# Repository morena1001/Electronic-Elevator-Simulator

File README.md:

# Electronic-Elevator-Simulator

This project simulates a single elevator that services a three floor building. A guest is able to request usage of the elevator in any floor, which will either be serviced immediately by the elevator, or be picked up while the elevator is on route to a destination in another floor. Inside the elevator, a guest is able to choose a not already chosen destination. This project was developed using an STM32F302R8 alongside a PCB housing the external buttons and LEDs.

In terms of inputs, there are a total of 7 input buttons. The first 4 correspond to the request buttons located outside of the elevator (one each for floors 1 and 3, which only go in one direction, and two for floor 2, which guests can choose to go upwards or downwards from). The other 3 inputs buttons  correspond to the destination buttons located inside of the elevator (one for each floor). 

In terms of outputs, there are a total of 12 LEDs. The first 3 display the current position of the elevator (one for each floor), the next 3 display the current destination of the elevator (one for each floor), the next 2 display the current direction of the elevator (one for each possible direction, up and down), the next 3 correspond to the request made to use the elevator (one for each floor), and the last LED blinks at regular intervals to show that a destination can be chosen.

## GPIO PERIPHERALS

**_PB0_** - CN7 pin 34, A3

Defined as II1 in the program, or _Inside Interface 1_, this pin connects to the external button in charge of setting floor 1 as a destination.

**_PB1_** - CN10 pin 24, D8

Defined as II2 in the program, this pin connects to the external button in charge of setting floor 2 as a destination.

**_PB2_** - CN10 pin 22, D7

Defined as II3 in the program, this pin connects to the external button in charge of setting floor 3 as a destination.

**_PB3_** - CN10 pin 31, D3

Defined as OI1U, or _Outside Interface 1 Up_, this pin connects to the external button in charge of requesting floor 1 with an upward direction.

**_PB4_** - CN10 pin 27, D5

Defined as OI2D, or _Outside Interface 2 Down_, this pin connects to the external button in charge of requesting floor 2 with a downward direction.

**_PB5** - CN10 pin 29, D4

Defined as OI2U, this pin connects to the external button in charge of requesting floor 2 with an upward direction.

**_PB6_** - CN10 pin 17, D10

Defined as OI3D, this pin connects to the external button in charge of requesting floor 3 with a downward direction.

**_PC0_** - CN7 pin 38, A5

Defined as PF1, or _Position Floor 1_, this pin connects to the external LED in charge of displaying floor 1 as the elevator's current position.

**_PC1_** - CN7 pin 36, A4

Defined as PF2, this pin connects to the external LED in charge of displaying floor 2 as the elevator's current position.

**_PC2_** - CN7 pin 35, A4

Defined as PF3, this pin connects to the external LED in charge of displaying floor 3 as the elevator's current position.

**_PC3_** - CN7 pin 37, A5

Defined as DF1, or _Destination Floor 1_, this pin connects to the external LED in charge of displaying floor 1 as a destination.

**_PC4_** - CN10 pin 34,D2

Defined as DF2, this pin connects to the external LED in charge of displaying floor 2 as a destination.

**_PC5_** - CN10 pin 6, D14

Defined as DF3, this pin connects to the external LED in charge of displaying floor 3 as a destination.

**_PC6_** - CN10 pin 4, D15

Defined as DU, or _Direction Up_, this pin connects to the external LED in charge of displaying the elevator's upward direction when moving.

**_PC7_** - CN10 pin 19, D9

Defined as DD, or _Direction Down_, this pin connects to the external LED in charge of displaying the elevator's downward direction when moving.

**_PC8_** - CN10 pin 2, above D15

Defined as FR1, or _Floor Request 1_, this pins connects to the external LED in charge of displaying floor 1's request to use the elevator.

**_PC9_** - CN10 pin 1, above D15

Defined as FR2, this pins connects to the external LED in charge of displaying floor 2's request to use the elevator.

**_PC10_** - CN7 pin 1

Defined as FR3, this pins connects to the external LED in charge of displaying floor 3's request to use the elevator.

**_PC11_** - CN7 pin 2

Defined as BCDI, or _Button Choose Destination Indicator_, this pin connects to the external LED in charge of blinking a certain pattern to show that a destination can be chosen.

## BUTTON AND LED GPIO CONFIGURATIONS

All of the external buttons are configured as follows. GPIO mode is set to "External Interrupt Mode with Rising edge trigger detection", and GPIO Pull-up/Pull-down is set to "Pull up". All of the external LEDs are configured as follows. GPIO output level is set to "Low", GPIO mode is set to "Output Push Pull", GPIO Pull-up/Pull-down is set to "No pull-up and no pull-down" and Maximum output speed is set to "Low".

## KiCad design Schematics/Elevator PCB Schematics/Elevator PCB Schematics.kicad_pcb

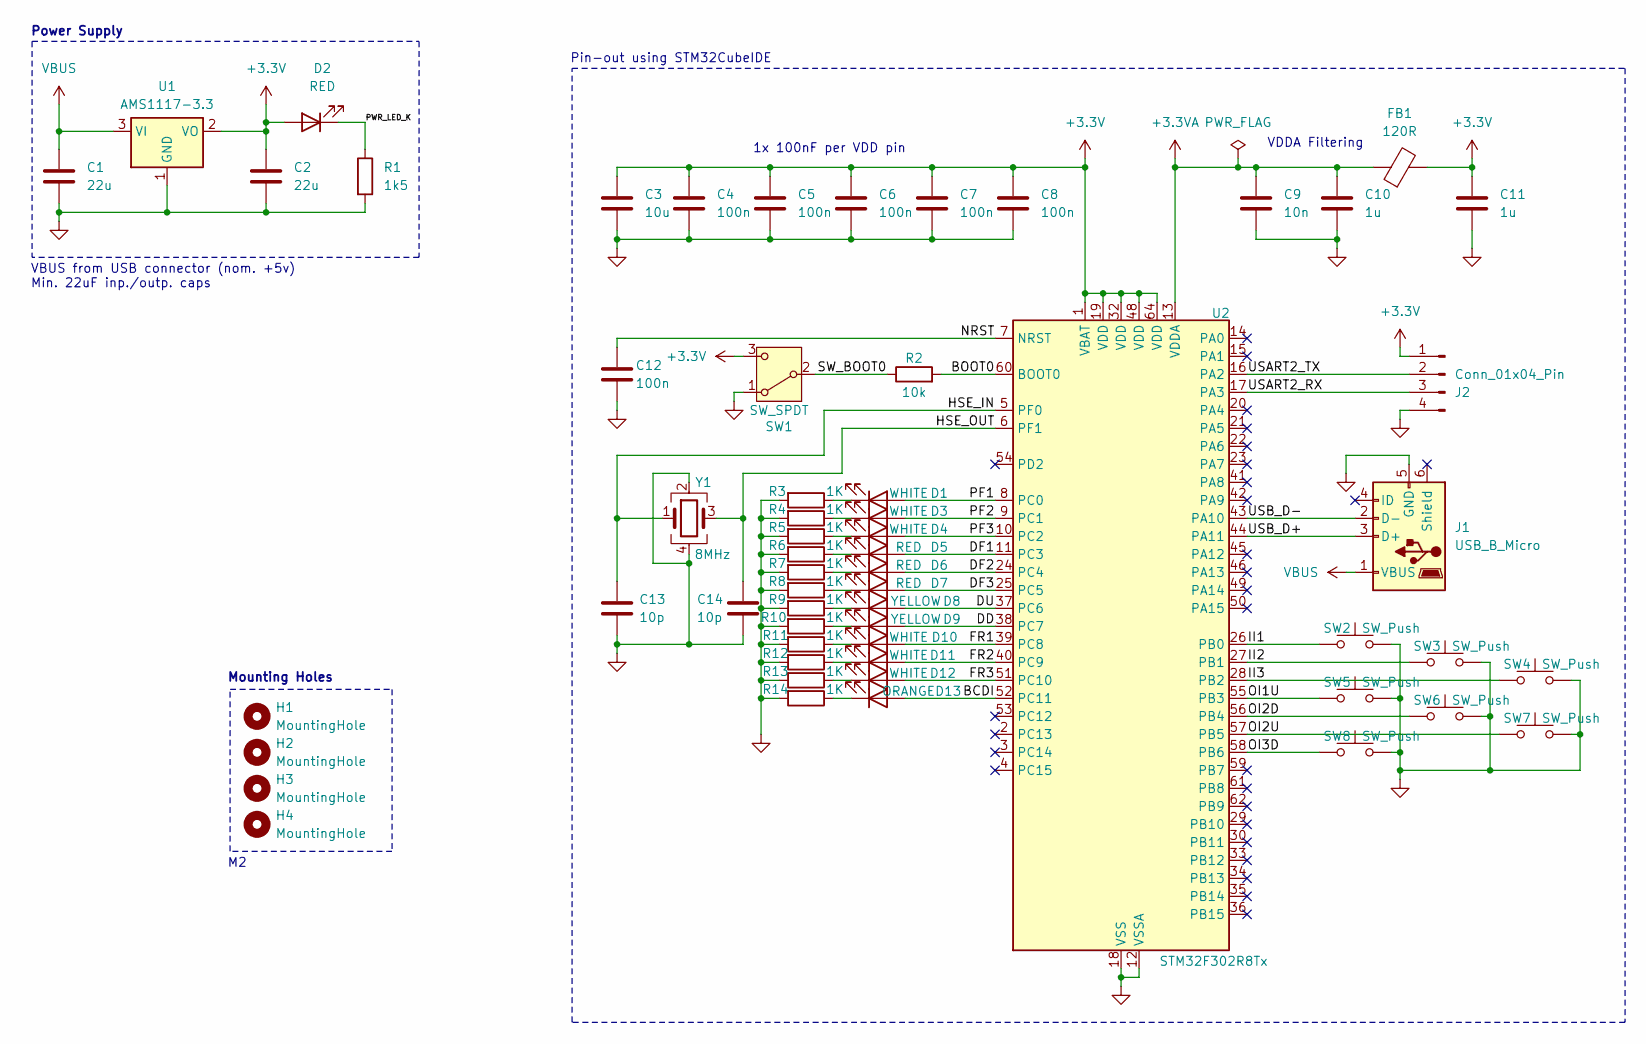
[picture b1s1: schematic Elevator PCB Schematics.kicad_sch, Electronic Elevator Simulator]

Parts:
C1, C2: 22u; C_0805_2012Metric
C3: 10u; C_0603_1608Metric
C4, C5, C6, C7, C8, C12: 100n; C_0402_1005Metric
C9: 10n; C_0402_1005Metric
C10, C11: 1u; C_0402_1005Metric
C13, C14: 10p; C_0402_1005Metric
D1, D3, D4, D10, D11, D12: WHITE; LED_0603_1608Metric
D2, D5, D6, D7: RED; LED_0603_1608Metric
D8, D9: YELLOW; LED_0603_1608Metric
D13: ORANGE; LED_0603_1608Metric
FB1: 120R; L_0603_1608Metric
H1, H2, H3, H4: MountingHole; MountingHole_2.2mm_M2
J1: USB_B_Micro; USB_Micro-B_Wuerth_629105150521
J2: Conn_01x04_Pin; PinHeader_1x04_P2.54mm_Vertical
R1: 1k5; R_0402_1005Metric
R2: 10k; R_0402_1005Metric
R3, R4, R5, R6, R7, R8, R9, R10, R11, R12, R13, R14: 1K; R_0402_1005Metric
SW1: SW_SPDT; SW_SPDT_PCM12
SW2, SW3, SW4, SW5, SW6, SW7, SW8: SW_Push; SW_PUSH_6mm_H5mm
U1: AMS1117-3.3; SOT-223-3_TabPin2
U2: STM32F302R8Tx; LQFP-64_10x10mm_P0.5mm
Y1: 8MHz; Crystal_SMD_0603-4Pin_6.0x3.5mm

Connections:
+3.3V: C2.1, C3.1, C4.1, C5.1, C6.1, C7.1, C8.1, C11.1, D2.2 (A), FB1.2, J2.1, SW1.3 (C), U1.2 (VO), U2.1 (VBAT), U2.19 (VDD), U2.32 (VDD), U2.48 (VDD), U2.64 (VDD)
+3.3VA: C9.1, C10.1, FB1.1, U2.13 (VDDA)
/BCDI: D13.2 (A), U2.52 (PC11)
/BOOT0: R2.2, U2.60 (BOOT0)
/DD: D9.2 (A), U2.38 (PC7)
/DF1: D5.2 (A), U2.11 (PC3)
/DF2: D6.2 (A), U2.24 (PC4)
/DF3: D7.2 (A), U2.25 (PC5)
/DU: D8.2 (A), U2.37 (PC6)
/FR1: D10.2 (A), U2.39 (PC8)
/FR2: D11.2 (A), U2.40 (PC9)
/FR3: D12.2 (A), U2.51 (PC10)
/HSE_IN: C13.1, U2.5 (PF0), Y1.1
/HSE_OUT: C14.1, U2.6 (PF1), Y1.3
/II1: SW2.1, U2.26 (PB0)
/II2: SW3.1, U2.27 (PB1)
/II3: SW4.1, U2.28 (PB2)
/NRST: C12.1, U2.7 (NRST)
/OI1U: SW5.1, U2.55 (PB3)
/OI2D: SW6.1, U2.56 (PB4)
/OI2U: SW7.1, U2.57 (PB5)
/OI3D: SW8.1, U2.58 (PB6)
/PF1: D1.2 (A), U2.8 (PC0)
/PF2: D3.2 (A), U2.9 (PC1)
/PF3: D4.2 (A), U2.10 (PC2)
/PWR_LED_K: D2.1 (K), R1.1
/SW_BOOT0: R2.1, SW1.2 (B)
/USART2_RX: J2.3, U2.17 (PA3)
/USART2_TX: J2.2, U2.16 (PA2)
/USB_D+: J1.3 (D+), U2.44 (PA11)
/USB_D-: J1.2 (D-), U2.43 (PA10)
GND: C1.2, C2.2, C3.2, C4.2, C5.2, C6.2, C7.2, C8.2, C9.2, C10.2, C11.2, C12.2, C13.2, C14.2, J1.5 (GND), J2.4, R1.2, R3.2, R4.2, R5.2, R6.2, R7.2, R8.2, R9.2, R10.2, R11.2, R12.2, R13.2, R14.2, SW1.1 (A), SW2.2, SW3.2, SW4.2, SW5.2, SW6.2, SW7.2, SW8.2, U1.1 (GND), U2.12 (VSSA), U2.18 (VSS), U2.31 (VSS), U2.47 (VSS), U2.63 (VSS), Y1.2, Y1.4
unnamed: D1.1 (K), R3.1
unnamed: D3.1 (K), R4.1
unnamed: D4.1 (K), R5.1
unnamed: D5.1 (K), R6.1
unnamed: D6.1 (K), R7.1
unnamed: D7.1 (K), R8.1
unnamed: D8.1 (K), R9.1
unnamed: D9.1 (K), R10.1
unnamed: D10.1 (K), R11.1
unnamed: D11.1 (K), R12.1
unnamed: D12.1 (K), R13.1
unnamed: D13.1 (K), R14.1
VBUS: C1.1, J1.1 (VBUS), U1.3 (VI)

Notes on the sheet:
Power Supply
Pin-out using STM32CubeIDE
VDDA Filtering
1x 100nF per VDD pin
Mounting Holes
VBUS from USB connector (nom. +5v) Min. 22uF inp./outp. caps

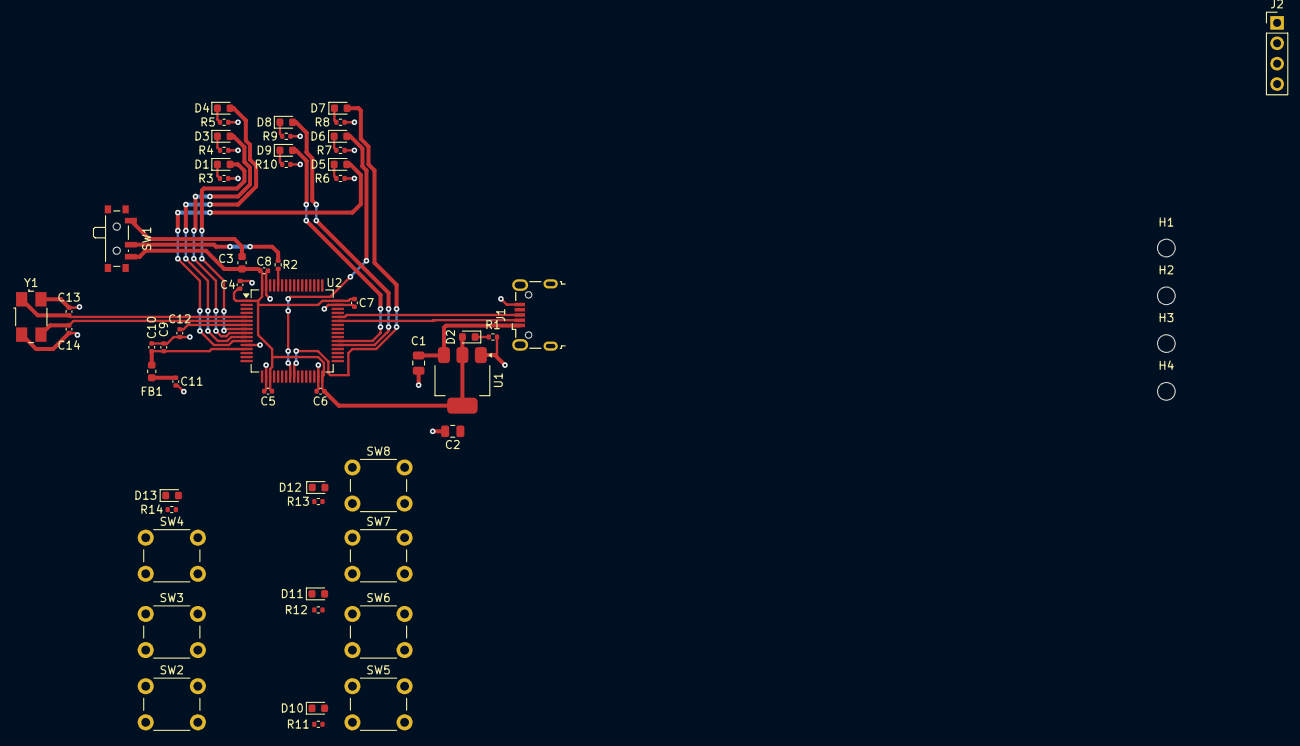
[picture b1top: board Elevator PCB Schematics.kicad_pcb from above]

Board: 2 copper layers, 59 parts (0 on the bottom side), 45 nets.

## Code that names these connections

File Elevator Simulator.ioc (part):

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Mcu.Name=STM32F302R(6-8)Tx
Mcu.Package=LQFP64
Mcu.UserName=STM32F302R8Tx
PA2.Mode=Asynchronous
PA2.Signal=USART2_TX
PA3.Mode=Asynchronous
PA3.Signal=USART2_RX
PB0.GPIOParameters=GPIO_PuPd,GPIO_Label,GPIO_ModeDefaultEXTI
PB0.GPIO_Label=II1 [Inside Interface 1]
PB0.GPIO_ModeDefaultEXTI=GPIO_MODE_IT_RISING
PB0.GPIO_PuPd=GPIO_PULLUP
PB0.Signal=GPXTI0
PB1.GPIOParameters=GPIO_PuPd,GPIO_Label,GPIO_ModeDefaultEXTI
PB1.GPIO_Label=II2 [Inside Interface 2]
PB1.GPIO_ModeDefaultEXTI=GPIO_MODE_IT_RISING
PB1.GPIO_PuPd=GPIO_PULLUP
PB1.Signal=GPXTI1
PB13.GPIOParameters=GPIO_Label
PB13.GPIO_Label=LD2 [Green Led]
PB13.Signal=GPIO_Output
PB2.GPIOParameters=GPIO_PuPd,GPIO_Label,GPIO_ModeDefaultEXTI
PB2.GPIO_Label=II3 [Inside Interface 3]
PB2.GPIO_ModeDefaultEXTI=GPIO_MODE_IT_RISING
PB2.GPIO_PuPd=GPIO_PULLUP
PB2.Signal=GPXTI2
PB3.GPIOParameters=GPIO_PuPd,GPIO_Label,GPIO_ModeDefaultEXTI
PB3.GPIO_Label=OI1U [Outside Interface 1 Up]
PB3.GPIO_ModeDefaultEXTI=GPIO_MODE_IT_RISING
PB3.GPIO_PuPd=GPIO_PULLUP
PB3.Signal=GPXTI3
PB4.GPIOParameters=GPIO_PuPd,GPIO_Label,GPIO_ModeDefaultEXTI
PB4.GPIO_Label=OI2D [Outside Interface 2 Down]
PB4.GPIO_ModeDefaultEXTI=GPIO_MODE_IT_RISING
PB4.GPIO_PuPd=GPIO_PULLUP
PB4.Signal=GPXTI4
PB5.GPIOParameters=GPIO_PuPd,GPIO_Label,GPIO_ModeDefaultEXTI
PB5.GPIO_Label=OI2U [Outside Interface 2 Up]
PB5.GPIO_ModeDefaultEXTI=GPIO_MODE_IT_RISING
PB5.GPIO_PuPd=GPIO_PULLUP
PB5.Signal=GPXTI5
PB6.GPIOParameters=GPIO_PuPd,GPIO_Label,GPIO_ModeDefaultEXTI
PB6.GPIO_Label=OI3D [Outside Interface 3 Down]
PB6.GPIO_ModeDefaultEXTI=GPIO_MODE_IT_RISING
PB6.GPIO_PuPd=GPIO_PULLUP
PB6.Signal=GPXTI6
PC0.GPIOParameters=GPIO_Label
PC0.GPIO_Label=PF1 [Position Floor 1]
PC0.Signal=GPIO_Output
PC1.GPIOParameters=GPIO_Label
PC1.GPIO_Label=PF2 [Position Floor 2]
PC1.Signal=GPIO_Output
PC10.GPIOParameters=GPIO_Label
PC10.GPIO_Label=FR3 [Floor Request 3]
PC10.Signal=GPIO_Output
PC11.GPIOParameters=GPIO_Label
PC11.GPIO_Label=BCDI [Blinking Choose Destination Indicator]
PC11.Signal=GPIO_Output
PC13.GPIOParameters=GPIO_Label,GPIO_ModeDefaultEXTI
PC13.GPIO_Label=B1 [Blue PushButton]
PC13.GPIO_ModeDefaultEXTI=GPIO_MODE_IT_FALLING
PC13.Signal=GPXTI13
PC2.GPIOParameters=GPIO_Label
PC2.GPIO_Label=PF3 [Position Floor 3]
PC2.Signal=GPIO_Output
PC3.GPIOParameters=GPIO_Label
PC3.GPIO_Label=DF1 [Destination Floor 1]
PC3.Signal=GPIO_Output
PC4.GPIOParameters=GPIO_Label
PC4.GPIO_Label=DF2 [Destination Floor 2]
PC4.Signal=GPIO_Output
PC5.GPIOParameters=GPIO_Label
PC5.GPIO_Label=DF3 [Destination Floor 3]
PC5.Signal=GPIO_Output
PC6.GPIOParameters=GPIO_Label
PC6.GPIO_Label=DU [Direction Up]
PC6.Signal=GPIO_Output
PC7.GPIOParameters=GPIO_Label
PC7.GPIO_Label=DD [Direction Down]
PC7.Signal=GPIO_Output
PC8.GPIOParameters=GPIO_Label
PC8.GPIO_Label=FR1 [Floor Request 1]
PC8.Signal=GPIO_Output
PC9.GPIOParameters=GPIO_Label
PC9.GPIO_Label=FR2 [Floor Request 2]
PC9.Signal=GPIO_Output
RCC.HSEPLLFreq_Value=8000000
RCC.HSE_VALUE=8000000
RCC.SYSCLKFreq_VALUE=8000000
board=custom

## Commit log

2024-07-25 Pre requests pointer type
2024-07-25 Updated to non-polling methods
2024-07-26 NEED TO TEST IT
2024-07-27 WORKS
2024-08-06 Schematics Added
